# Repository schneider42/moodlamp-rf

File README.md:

# moodlamp
The moodlamp allows to change color in RGB colorspace.

Some art has been done with the help of moodlamps:
- ACAB (AllColourAreBeautiful) https://wiki.muc.ccc.de/acab:start
- Die Drei C https://wiki.muc.ccc.de/diedreic

# r3 version and earlier versions
Earlier versions are developed with ATmega324P, ATmega644P, ... For RS485 usage, change the MCU section in the file ubloader/Makefile.

# r4 version (2th quarter 2015)
Latest r4 version is designed with ATmega324A. If you get a warning from avrdude "device signature [..] expected signature [..] or use -F to override this check", put the following lines in your avrdude.conf:
```diff
 #------------------------------------------------------------
+# ATmega324A
+#------------------------------------------------------------
+
+# similar to ATmega324P
+
+part parent "m324p"
+    id               = "m324a";
+    desc             = "ATmega324A";
+    signature        = 0x1e 0x95 0x15;
+
+    ocdrev           = 3;
+  ;
+
+#------------------------------------------------------------
 # ATmega324PA
 #------------------------------------------------------------
```
For RS485 usage, also double check the MCU part in the file ubloader/Makefile.

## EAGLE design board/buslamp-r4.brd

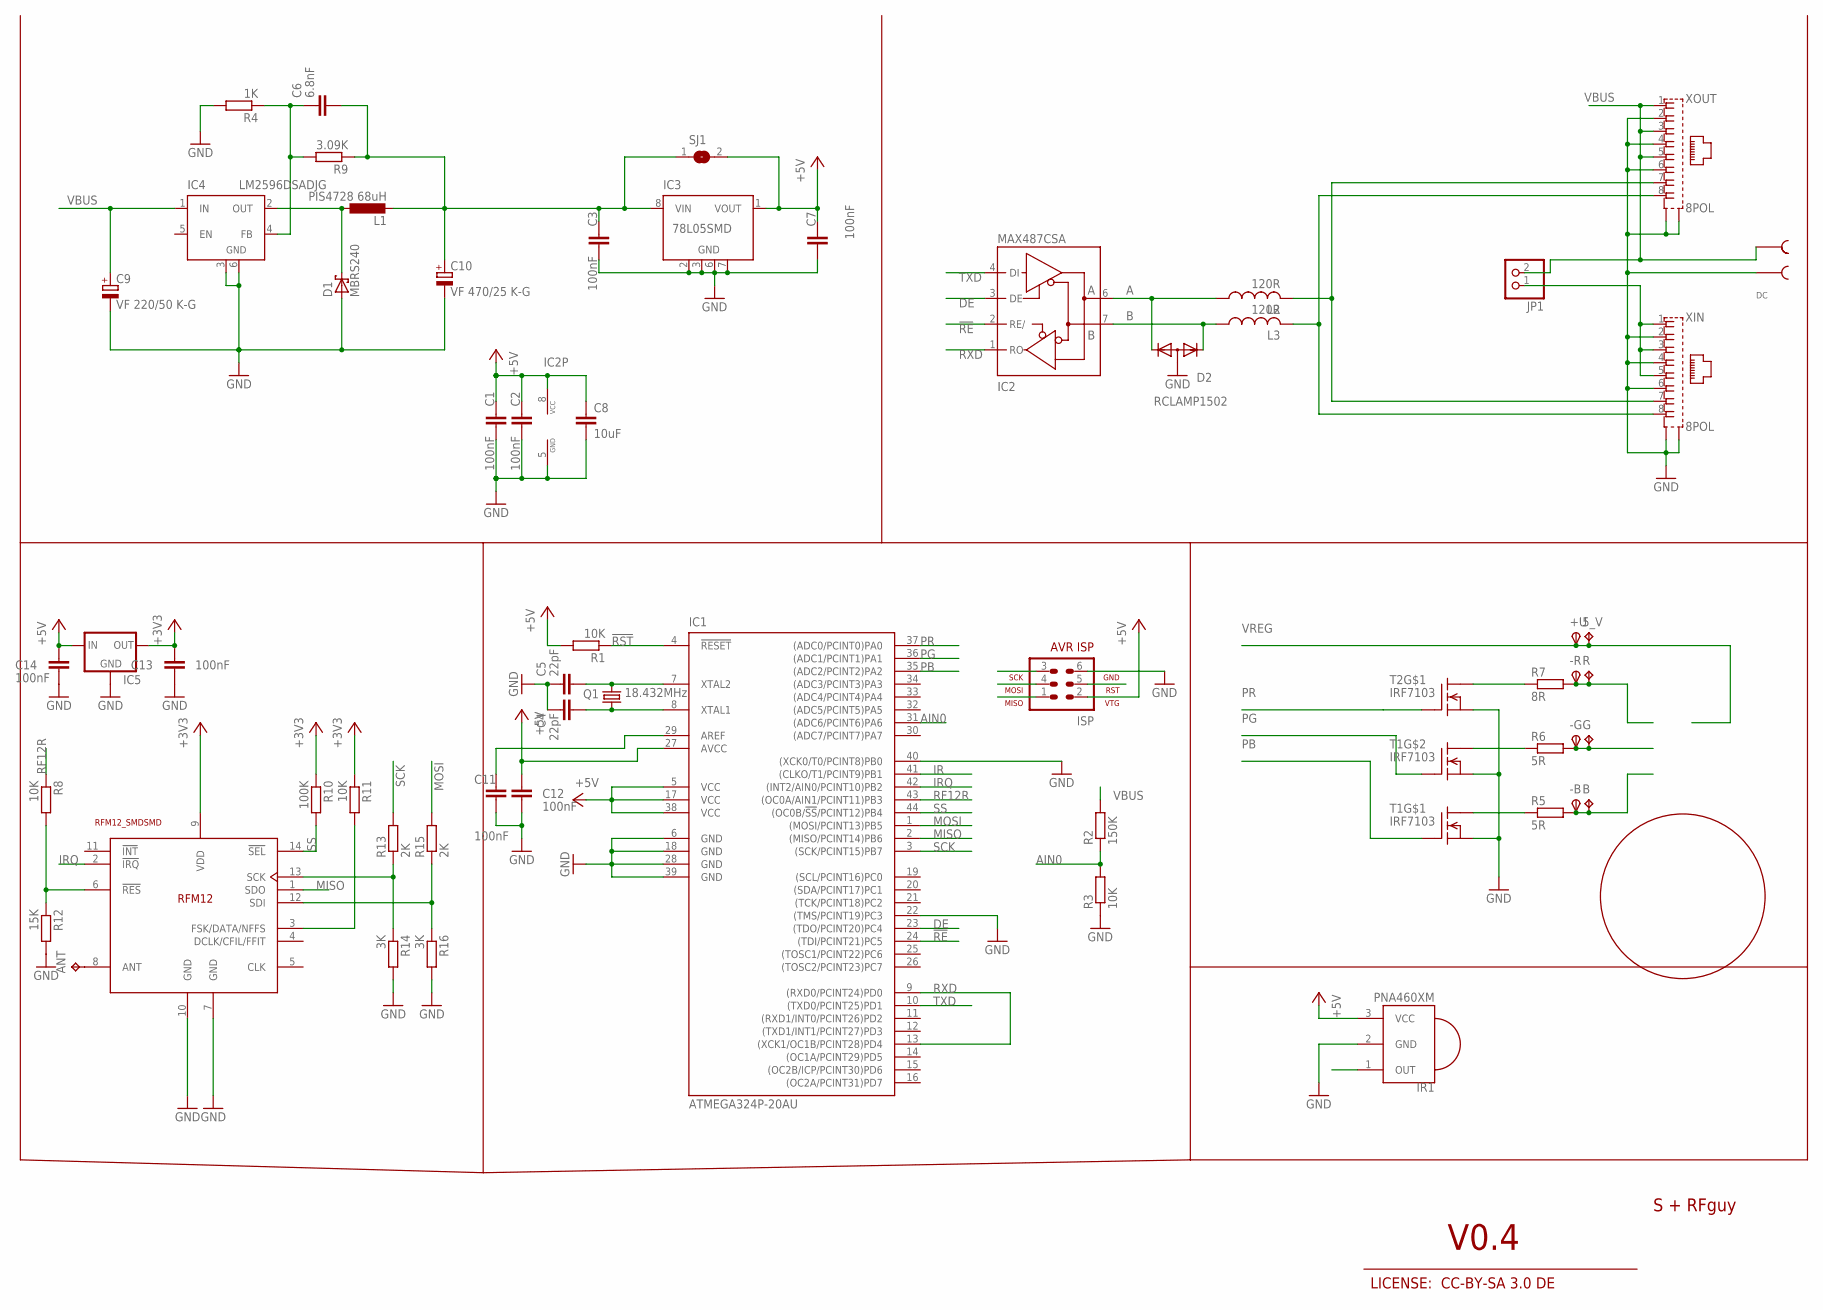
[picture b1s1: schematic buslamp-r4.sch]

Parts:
5_V: TPPAD1-13; P1-13
+U: TPSTP212R; TP212R
-B: TPSTP212R; TP212R
-G: TPSTP212R; TP212R
-R: TPSTP212R; TP212R
ANT: TPPAD1-13; P1-13
B: TPPAD1-13; P1-13
C1, C2, C3, C7: 100nF; C0805K
C4, C5: 22pF; C0805K
C6: 6.8nF; C0805K
C8: 10uF; C1210
C9: VF 220/50 K-G; UD-10X10_NICHICON
C10: VF 470/25 K-G; UD-10X10_NICHICON
C11, C12, C13, C14: 100nF; C0805
D1: MBRS240; SMB
D2: RCLAMP1502; SOT23
DC: STL-266-2
G: TPPAD1-13; P1-13
IC1: ATMEGA324P-20AU; TQFP44
IC2: MAX487CSA; SO08
IC3: 78L05SMD; SO08
IC4: LM2596DSADJG; TO263-5
IC5: MCP1700SOT23; SOT23
IR1: PNA460XM
ISP: AVR-ISP-6
JP1: PINHD-1X2; 1X02
L1: PIS4728 68uH; PIS4728
L2, L3: 120R; L0603
Q1: 18.432MHz; HC49/S
R: TPPAD1-13; P1-13
R1, R8, R11: 10K; M0805
R2: 150K; R0805
R3: 10K; R0805
R4: 1K; M0805
R5, R6: 5R; 0617/17
R7: 8R; 0617/17
R9: 3.09K; M0805
R10: 100K; M0805
R12: 15K; M0805
R13, R15: 2K; M0805
R14, R16: 3K; M0805
RF1: RFM12_SMDSMD; RFM12
SJ1: SJ
T1, T2: IRF7103; SO-8
U$2: KK-STERN; STERN
XIN: 8POL
XOUT: 8POL

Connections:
!RE: IC1.24 ((TDI/PCINT21)PC5), IC2.2 (RE/)
!RST: IC1.4 (!RESET), ISP.5, R1.1
+3V3: C13.2, IC5.2 (OUT), R10.1, R11.1, RF1.9 (VDD)
+5V: C1.1, C2.1, C7.1, C8.1, C12.2, C14.2, IC1.5 (VCC), IC1.17 (VCC), IC1.27 (AVCC), IC1.38 (VCC), IC2.8 (VCC), IC3.1 (VOUT), IC5.3 (IN), IR1.3 (VCC), ISP.2, R1.2, SJ1.2
A: L2.2, XIN.7, XOUT.7
AIN0: IC1.31 ((ADC6/PCINT6)PA6), R2.1, R3.2
B: L3.2, XIN.8, XOUT.8
DE: IC1.23 ((TDO/PCINT20)PC4), IC2.3 (DE)
G: -G.TP, G.TP, R6.2
GND: C1.2, C2.2, C3.2, C4.1, C5.1, C7.2, C8.2, C9.-, C10.-, C11.1, C12.1, C13.1, C14.1, D1.A, D2.3 (A), DC.P$3, IC1.6 (GND), IC1.18 (GND), IC1.22 ((TMS/PCINT19)PC3), IC1.28 (GND), IC1.39 (GND), IC1.40 ((XCK0/T0/PCINT8)PB0), IC2.5 (GND), IC3.2 (GND), IC3.3 (GND), IC3.6 (GND), IC3.7 (GND), IC4.3 (GND), IC4.6 (GND), IC5.1 (GND), IR1.2 (GND), ISP.6, R3.1, R4.2, R12.2, R14.2, R16.2, RF1.7 (GND), RF1.10 (GND), T1.1 (S), T1.3 (S), T2.1 (S), XIN.2, XIN.4, XIN.6, XIN.S1, XIN.S2, XOUT.2, XOUT.4, XOUT.6, XOUT.S1, XOUT.S2
IR: IC1.41 ((CLKO/T1/PCINT9)PB1), IR1.1 (OUT)
IRQ: IC1.42 ((INT2/AIN0/PCINT10)PB2), RF1.2 (!IRQ)
MISO: IC1.2 ((MISO/PCINT14)PB6), ISP.1, RF1.1 (SDO)
MOSI: IC1.1 ((MOSI/PCINT13)PB5), ISP.4, R15.2
unnamed: R7.1, T2.8 (D1)
unnamed: R8.2, R12.1, RF1.6 (!RES)
unnamed: C6.1, IC4.4 (FB), R4.1, R9.2
unnamed: R6.1, T1.5 (D1)
unnamed: R5.1, T1.8 (D1)
unnamed: -B.TP, B.TP, R5.2
unnamed: R13.1, R14.1, RF1.13 (SCK)
unnamed: R15.1, R16.1, RF1.12 (SDI)
unnamed: ANT.TP, RF1.8 (ANT)
unnamed: D1.C, IC4.2 (OUT), L1.1
unnamed: D2.2 (K2), IC2.6 (A), L2.1
unnamed: D2.1 (K1), IC2.7 (B), L3.1
unnamed: R11.2, RF1.3 (FSK/DATA/NFFS)
unnamed: C11.2, IC1.29 (AREF)
PB: IC1.35 ((ADC2/PCINT2)PA2), T1.2 (G)
PG: IC1.36 ((ADC1/PCINT1)PA1), T1.4 (G)
PR: IC1.37 ((ADC0/PCINT0)PA0), T2.2 (G)
R: -R.TP, R.TP, R7.2
RF12R: IC1.43 ((OC0A/AIN1/PCINT11)PB3), R8.1
RXD: IC1.9 ((RXD0/PCINT24)PD0), IC1.13 ((XCK1/OC1B/PCINT28)PD4), IC2.1 (RO)
SCK: IC1.3 ((SCK/PCINT15)PB7), ISP.3, R13.2
SS: IC1.44 ((OC0B/!SS!/PCINT12)PB4), R10.2, RF1.14 (!SEL)
TXD: IC1.10 ((TXD0/PCINT25)PD1), IC2.4 (DI)
VBUS: C9.+, DC.P$4, IC4.1 (IN), JP1.2, R2.2, XOUT.1, XOUT.3, XOUT.5
VBUSOUT: JP1.1, XIN.1, XIN.3, XIN.5
VREG: 5_V.TP, +U.TP, C3.1, C6.2, C10.+, IC3.8 (VIN), L1.2, R9.1, SJ1.1
XTAL1: C5.2, IC1.7 (XTAL2), Q1.2
XTAL2: C4.2, IC1.8 (XTAL1), Q1.1

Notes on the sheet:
S + RFguy
V0.4
LICENSE: CC-BY-SA 3.0 DE
RF12R
IRQ
MOSI
MISO
SCK

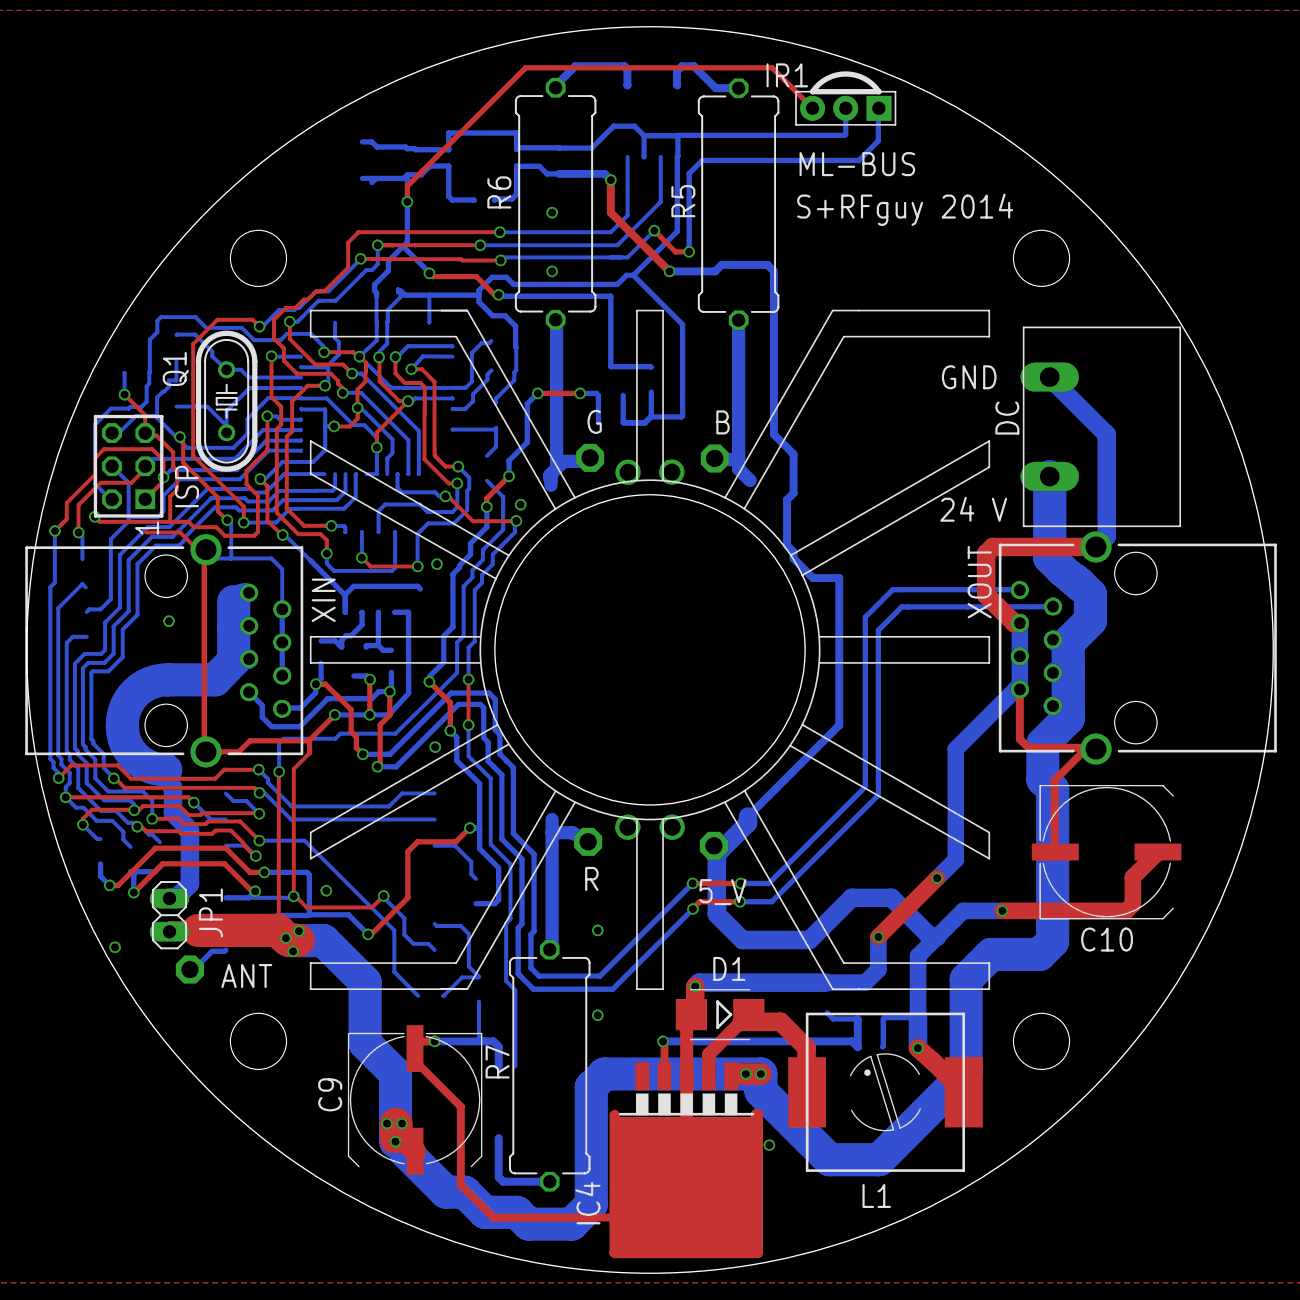
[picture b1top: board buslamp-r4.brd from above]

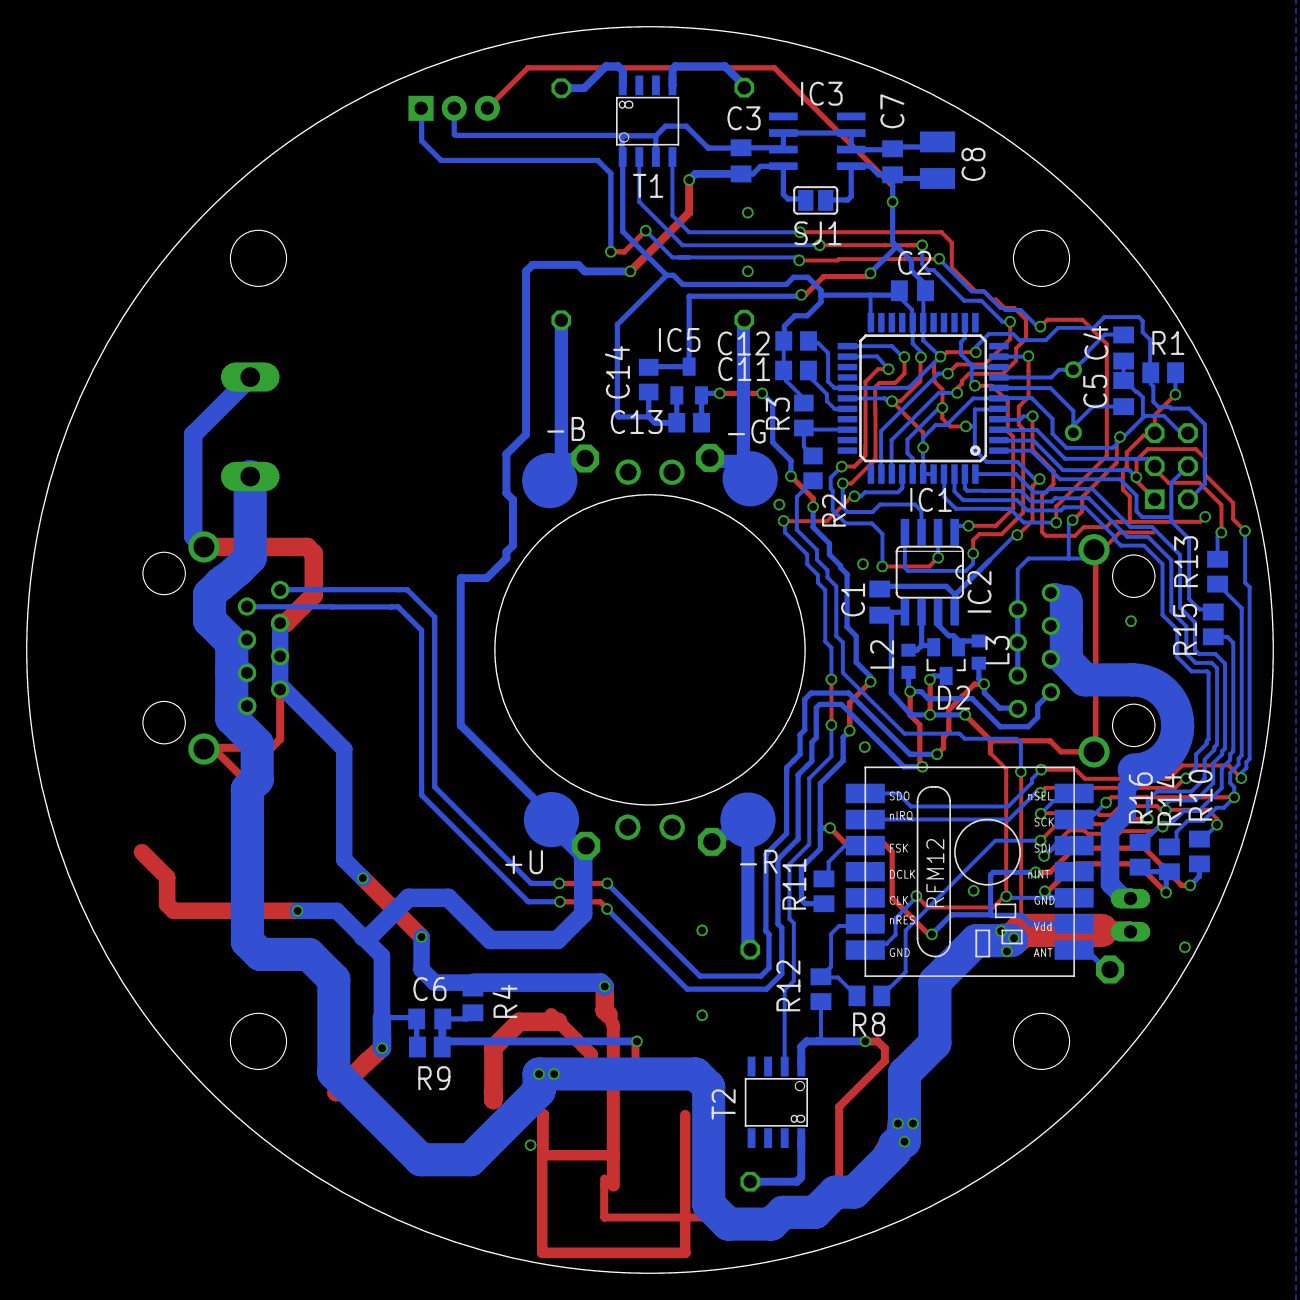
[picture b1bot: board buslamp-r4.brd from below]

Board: 2 copper layers, 95.5 x 95.5 mm, 61 parts (40 on the bottom side), 42 nets.

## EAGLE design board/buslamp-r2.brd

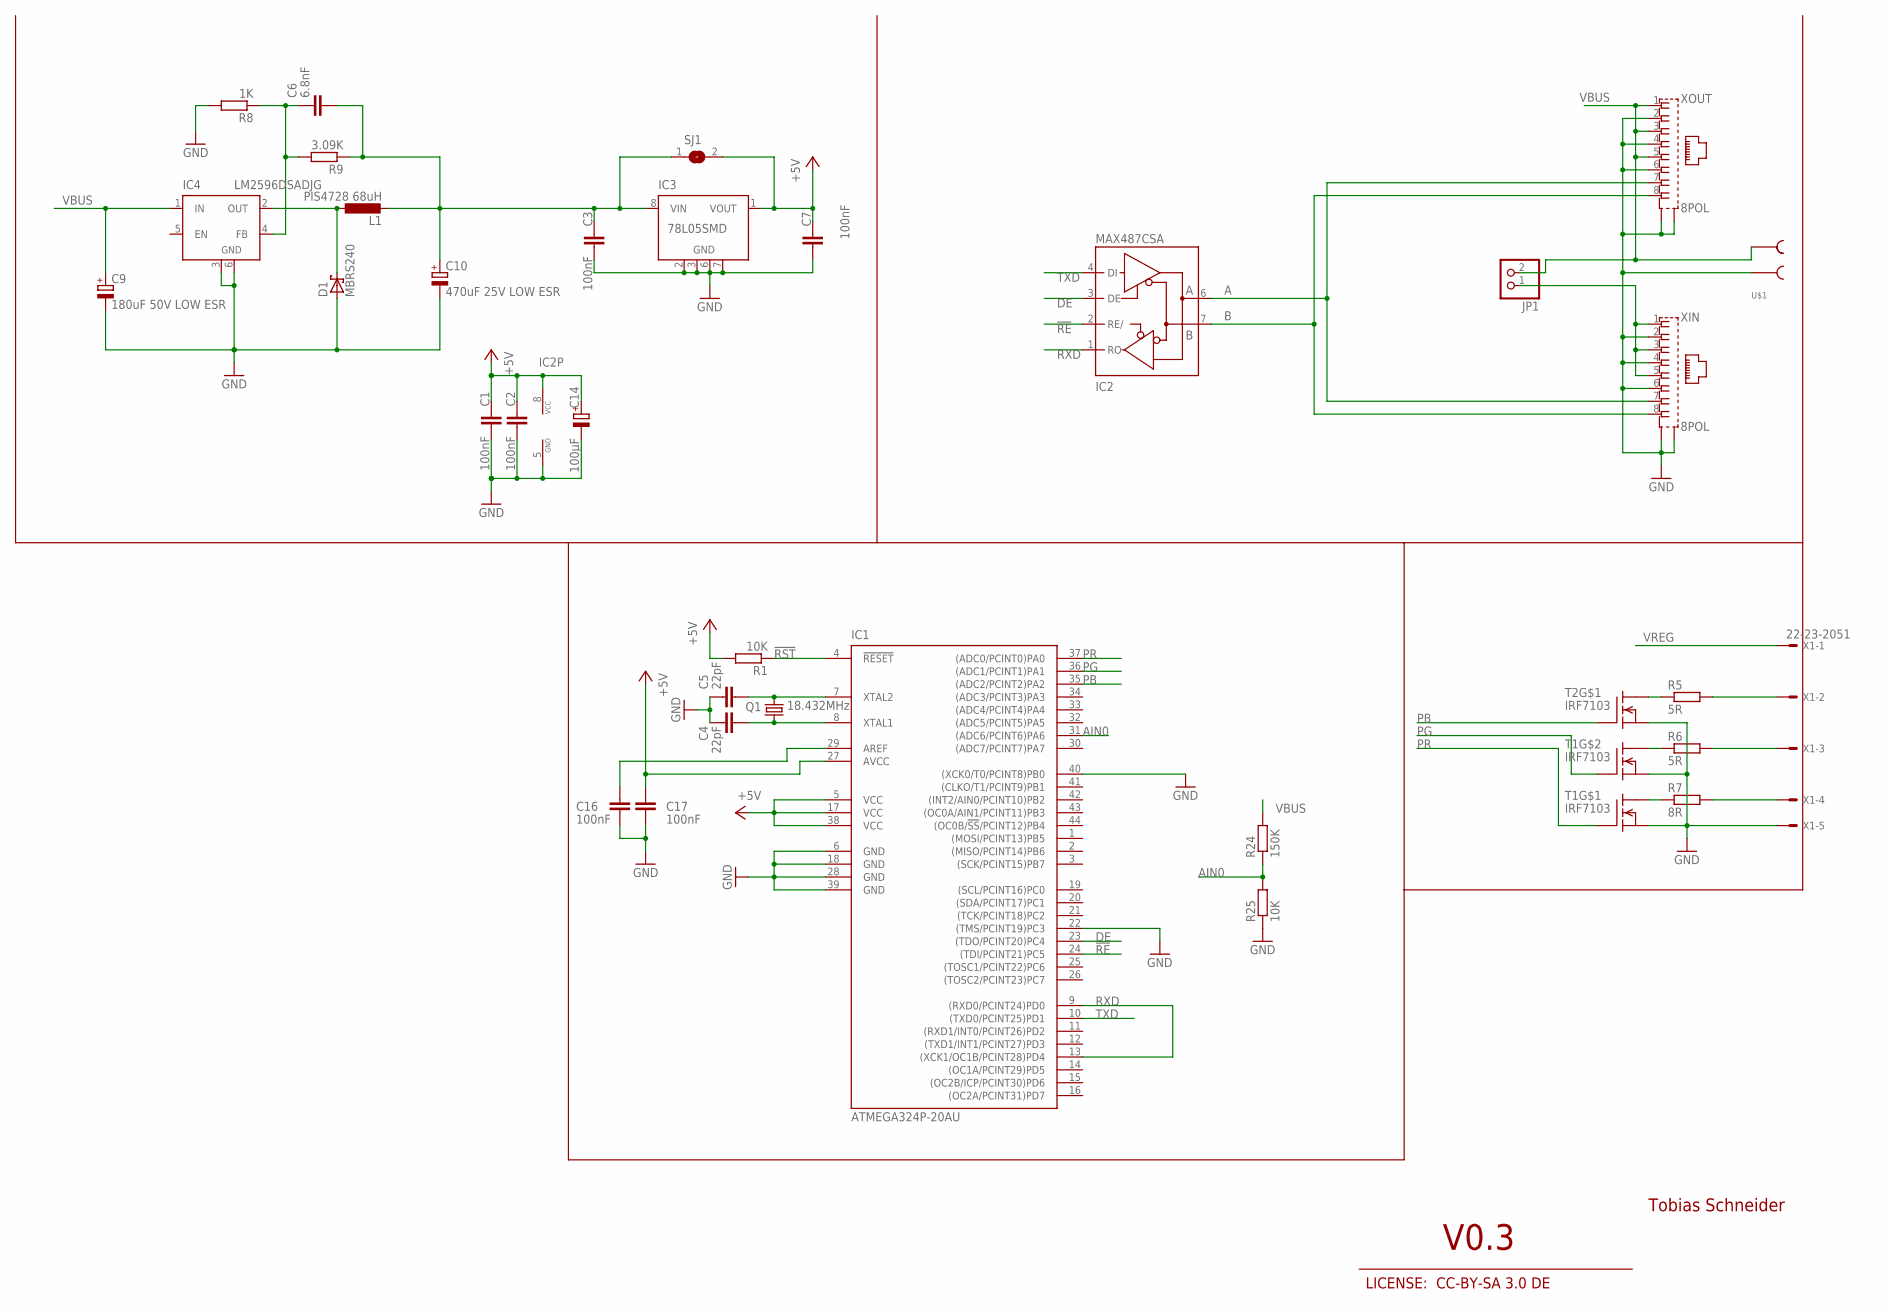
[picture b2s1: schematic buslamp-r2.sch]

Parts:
C1, C2, C3, C7: 100nF; C0805K
C4, C5: 22pF; C0805K
C6: 6.8nF; C0805K
C9: 180uF 50V LOW ESR; E3,5-8
C10: 470uF 25V LOW ESR; E2,5-7
C14: 100µF; E2,5-6
C16, C17: 100nF; C0805
D1: MBRS240; SMB
IC1: ATMEGA324P-20AU; TQFP44
IC2: MAX487CSA; SO08
IC3: 78L05SMD; SO08
IC4: LM2596DSADJG; TO263-5
JP1: PINHD-1X2; 1X02
L1: PIS4728 68uH; PIS4728
Q1: 18.432MHz; HC49/S
R1: 10K; M0805
R5, R6: 5R; 0617/17
R7: 8R; 0617/17
R8: 1K; M0805
R9: 3.09K; M0805
R24: 150K; R0805
R25: 10K; R0805
SJ1: SJ
T1, T2: IRF7103; SO-8
U$1: STL-266-2
X1: 22-23-2051
XIN: 8POL
XOUT: 8POL

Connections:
!RE: IC1.24 ((TDI/PCINT21)PC5), IC2.2 (RE/)
!RST: IC1.4 (!RESET), R1.1
+5V: C1.1, C2.1, C7.1, C14.+, C17.2, IC1.5 (VCC), IC1.17 (VCC), IC1.27 (AVCC), IC1.38 (VCC), IC2.8 (VCC), IC3.1 (VOUT), R1.2, SJ1.2
A: IC2.6 (A), XIN.7, XOUT.7
AIN0: IC1.31 ((ADC6/PCINT6)PA6), R24.1, R25.2
B: IC2.7 (B), XIN.8, XOUT.8
DE: IC1.23 ((TDO/PCINT20)PC4), IC2.3 (DE)
GND: C1.2, C2.2, C3.2, C4.1, C5.1, C7.2, C9.-, C10.-, C14.-, C16.1, C17.1, D1.A, IC1.6 (GND), IC1.18 (GND), IC1.22 ((TMS/PCINT19)PC3), IC1.28 (GND), IC1.39 (GND), IC1.40 ((XCK0/T0/PCINT8)PB0), IC2.5 (GND), IC3.2 (GND), IC3.3 (GND), IC3.6 (GND), IC3.7 (GND), IC4.3 (GND), IC4.6 (GND), R8.2, R25.1, T1.1 (S), T1.3 (S), T2.1 (S), U$1.P$3, X1.5, XIN.2, XIN.4, XIN.6, XIN.S1, XIN.S2, XOUT.2, XOUT.4, XOUT.6, XOUT.S1, XOUT.S2
unnamed: R7.1, T1.8 (D1)
unnamed: C6.1, IC4.4 (FB), R8.1, R9.2
unnamed: R6.1, T1.5 (D1)
unnamed: R5.1, T2.8 (D1)
unnamed: R7.2, X1.4
unnamed: R6.2, X1.3
unnamed: R5.2, X1.2
unnamed: D1.C, IC4.2 (OUT), L1.1
unnamed: C16.2, IC1.29 (AREF)
PB: IC1.35 ((ADC2/PCINT2)PA2), T2.2 (G)
PG: IC1.36 ((ADC1/PCINT1)PA1), T1.4 (G)
PR: IC1.37 ((ADC0/PCINT0)PA0), T1.2 (G)
RXD: IC1.9 ((RXD0/PCINT24)PD0), IC1.13 ((XCK1/OC1B/PCINT28)PD4), IC2.1 (RO)
TXD: IC1.10 ((TXD0/PCINT25)PD1), IC2.4 (DI)
VBUS: C9.+, IC4.1 (IN), JP1.2, R24.2, U$1.P$4, XOUT.1, XOUT.3, XOUT.5
VBUSOUT: JP1.1, XIN.1, XIN.3, XIN.5
VREG: C3.1, C6.2, C10.+, IC3.8 (VIN), L1.2, R9.1, SJ1.1, X1.1
XTAL1: C5.2, IC1.7 (XTAL2), Q1.2
XTAL2: C4.2, IC1.8 (XTAL1), Q1.1

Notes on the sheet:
Tobias Schneider
V0.3
LICENSE: CC-BY-SA 3.0 DE

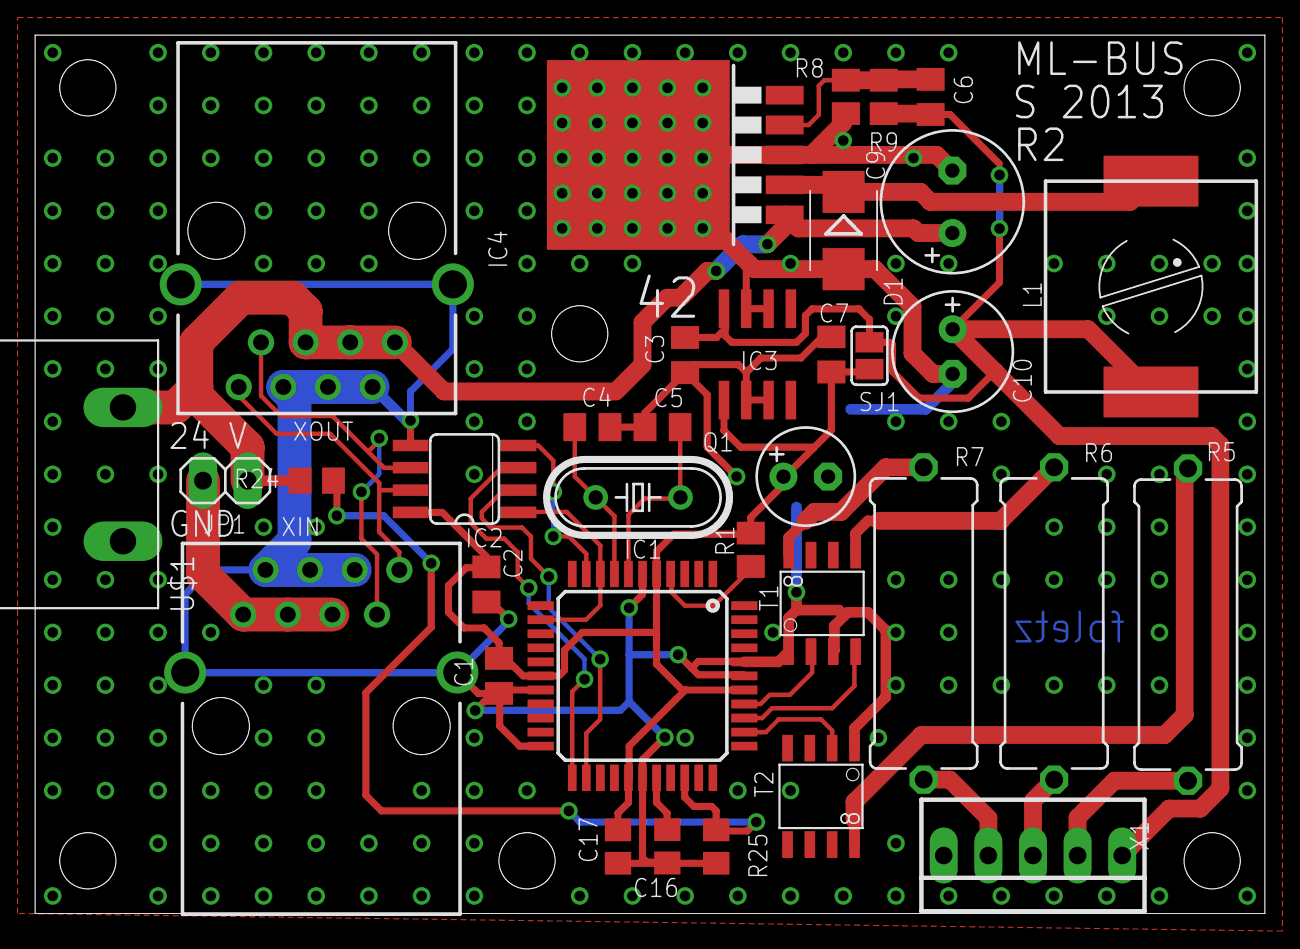
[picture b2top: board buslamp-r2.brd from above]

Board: 2 copper layers, 70.0 x 50.0 mm, 35 parts (0 on the bottom side), 27 nets.

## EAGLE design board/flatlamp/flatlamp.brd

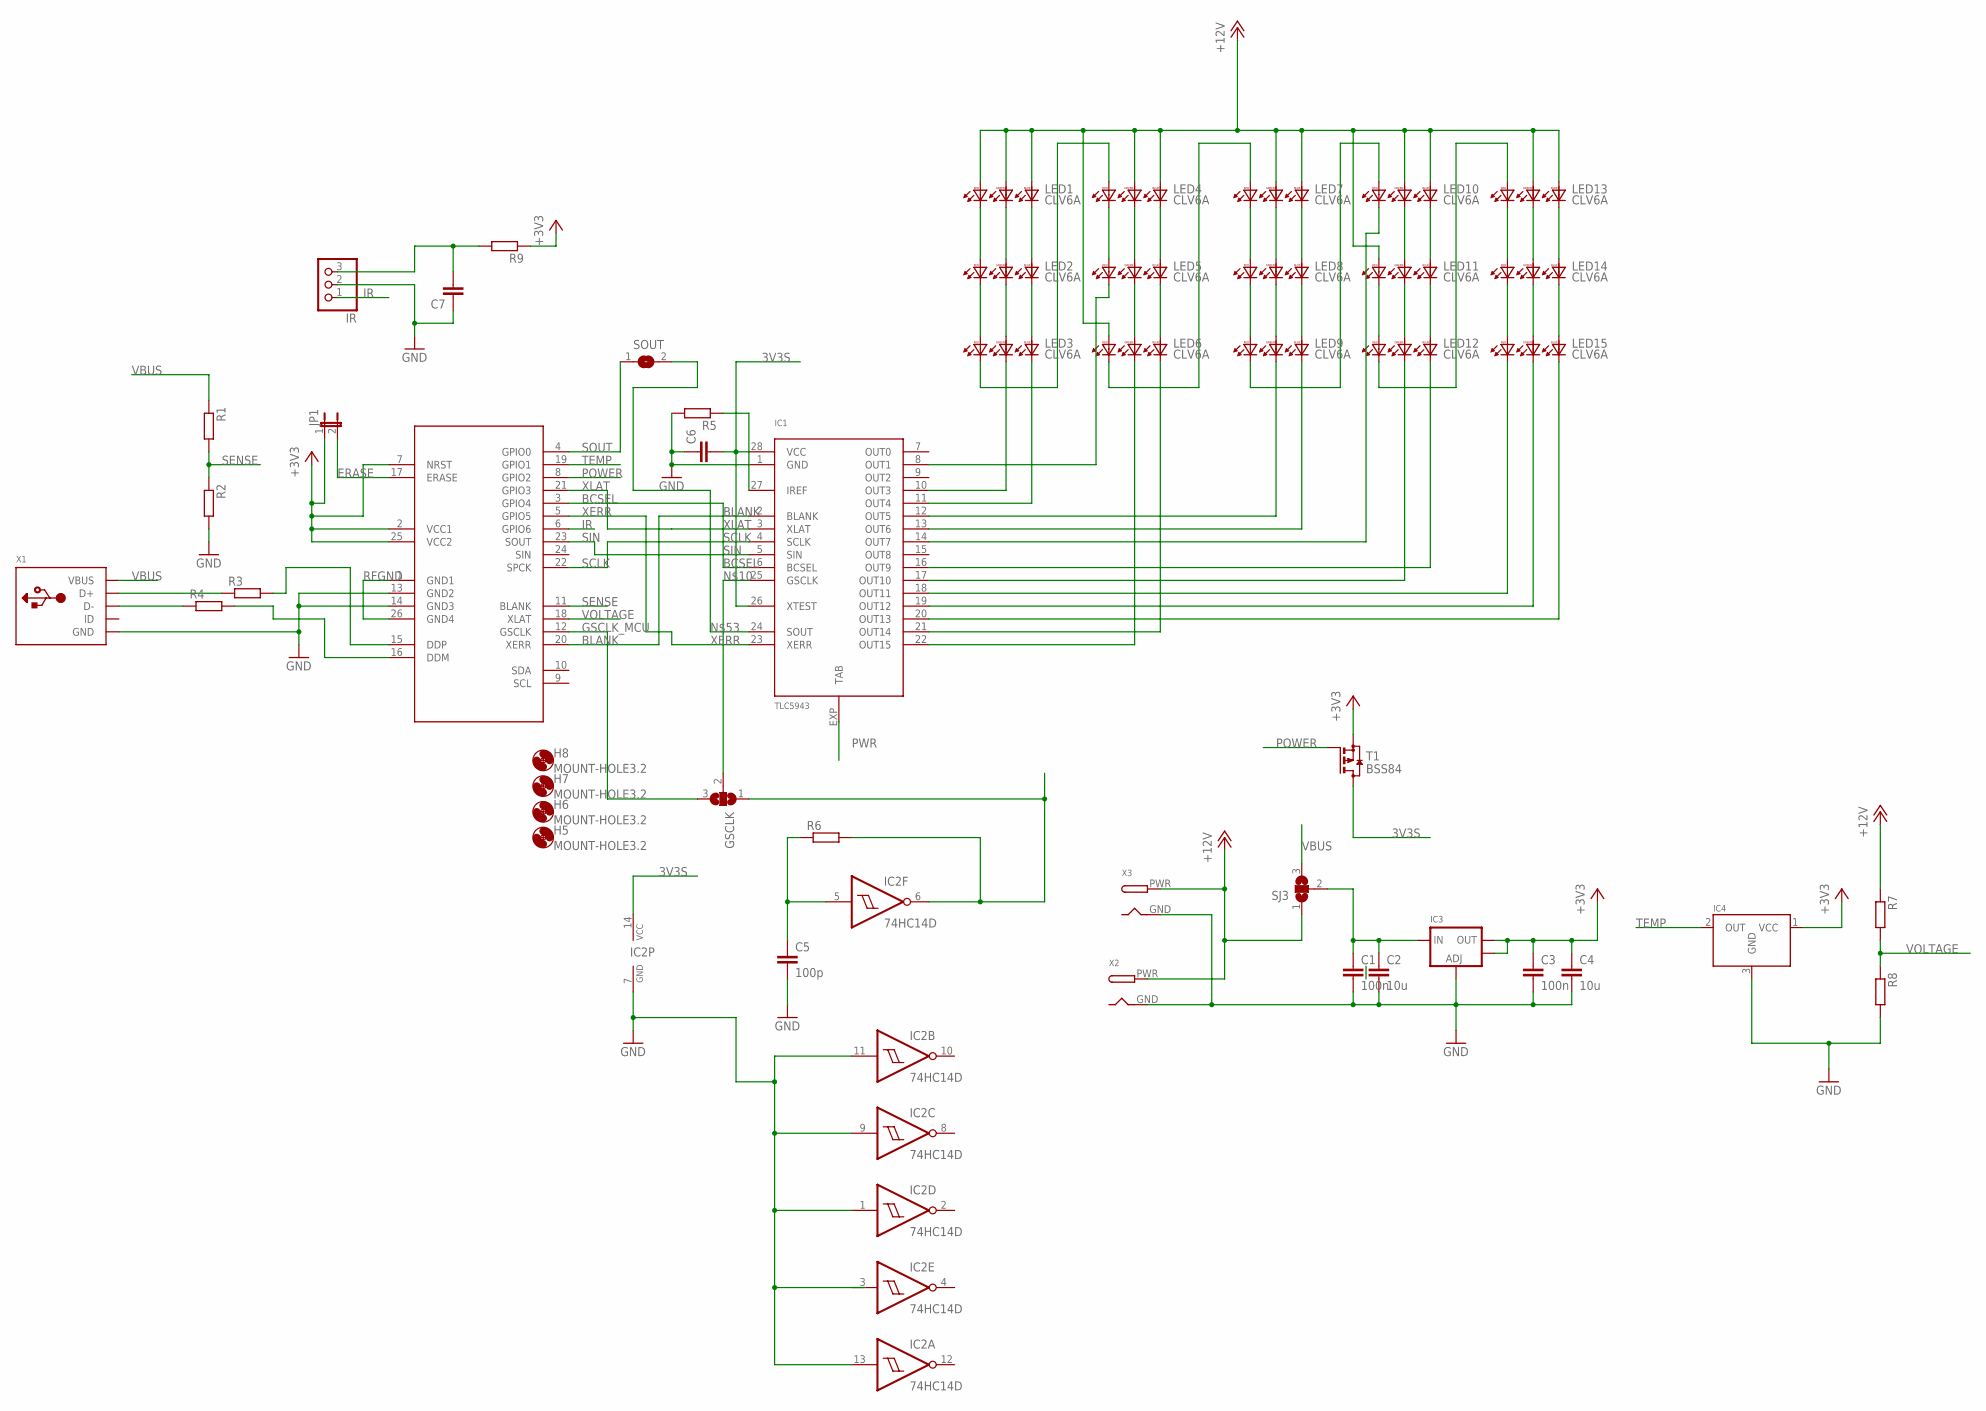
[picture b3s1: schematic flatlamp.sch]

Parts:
C1, C3: 100n; C0805
C2, C4: 10u; C0805
C5: 100p; C0805
C6, C7: C-EUC0805; C0805
GSCLK: SJ2W; SJ_2
H5, H6, H7, H8: MOUNT-HOLE3.2; 3,2
IC1: TLC5943; HTSSOP28PWP
IC2: 74HC14D; SO14
IC3: LM1117SOT223-REFLOW; SOT223-R
IC4: MCP9701T-E/TTCTREFLOW; SOT23-R
IR: PINHD-1X3; 1X03
JP1: JP1E; JP1
LED1, LED2, LED3, LED4, LED5, LED6, LED7, LED8, LED9, LED10, LED11, LED12, LED13, LED14, LED15: CLV6A; PLCC6
R1, R2, R3, R4, R5, R6, R7, R8, R9: R-EU_R0805; R0805
SJ3: SJ2W; SJ_2
SOUT: SJ
T1: BSS84; SOT23
U$1: RFBOARD
X1: USBMINIB; USB-MINIB
X2, X3: DCBARRELPTH; DCJACK_2MM_PTH

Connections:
3V3S: C6.2, IC1.26 (XTEST), IC1.28 (VCC), IC2.14 (VCC), T1.3 (D)
+3V3: C3.1, C4.1, IC3.2 (OUT), IC3.4 (OUT1), IC4.1 (VCC), JP1.1, R9.1, T1.2 (S), U$1.2 (VCC1), U$1.7 (NRST), U$1.25 (VCC2)
+12V: LED1.4 (RA), LED1.5 (GA), LED1.6 (BA), LED4.5 (GA), LED4.6 (BA), LED6.4 (RA), LED7.5 (GA), LED7.6 (BA), LED10.5 (GA), LED10.6 (BA), LED11.4 (RA), LED13.5 (GA), LED13.6 (BA), R7.1, SJ3.1, X2.PWR, X3.PWR
BCSEL: IC1.6 (BCSEL), U$1.3 (GPIO4)
BLANK: IC1.2 (BLANK), U$1.20 (XERR)
ERASE: JP1.2, U$1.17 (ERASE)
GND: C1.2, C2.2, C3.2, C4.2, C5.2, C6.1, C7.1, IC1.1 (GND), IC2.1 (I), IC2.7 (GND), IC2.9 (I), IC2.11 (I), IC2.13 (I), IC3.1 (ADJ), IC4.3 (GND), IR.2, R2.2, R5.2, R8.2, U$1.13 (GND2), U$1.14 (GND3), X1.GND, X2.GND, X3.GND
GSCLK_MCU: GSCLK.3, U$1.12 (GSCLK)
IR: IR.1, U$1.6 (GPIO6)
unnamed: LED1.3 (RC), LED2.4 (RA)
unnamed: LED1.2 (GC), LED2.5 (GA)
unnamed: LED1.1 (BC), LED2.6 (BA)
unnamed: LED2.3 (RC), LED3.4 (RA)
unnamed: LED2.2 (GC), LED3.5 (GA)
unnamed: LED2.1 (BC), LED3.6 (BA)
unnamed: LED4.3 (RC), LED5.4 (RA)
unnamed: LED4.2 (GC), LED5.5 (GA)
unnamed: LED4.1 (BC), LED5.6 (BA)
unnamed: GSCLK.2, IC1.25 (GSCLK)
unnamed: LED5.2 (GC), LED6.5 (GA)
unnamed: LED5.1 (BC), LED6.6 (BA)
unnamed: LED7.3 (RC), LED8.4 (RA)
unnamed: LED7.2 (GC), LED8.5 (GA)
unnamed: LED7.1 (BC), LED8.6 (BA)
unnamed: LED8.3 (RC), LED9.4 (RA)
unnamed: LED8.2 (GC), LED9.5 (GA)
unnamed: LED8.1 (BC), LED9.6 (BA)
unnamed: IC1.10 (OUT3), LED3.2 (GC)
unnamed: LED10.2 (GC), LED11.5 (GA)
unnamed: LED10.1 (BC), LED11.6 (BA)
unnamed: LED11.3 (RC), LED12.4 (RA)
unnamed: LED11.2 (GC), LED12.5 (GA)
unnamed: LED11.1 (BC), LED12.6 (BA)
unnamed: LED13.3 (RC), LED14.4 (RA)
unnamed: LED13.2 (GC), LED14.5 (GA)
unnamed: LED13.1 (BC), LED14.6 (BA)
unnamed: LED14.3 (RC), LED15.4 (RA)
unnamed: LED14.2 (GC), LED15.5 (GA)
unnamed: LED14.1 (BC), LED15.6 (BA)
unnamed: LED3.3 (RC), LED4.4 (RA)
unnamed: LED6.3 (RC), LED7.4 (RA)
unnamed: LED9.3 (RC), LED10.4 (RA)
unnamed: LED12.3 (RC), LED13.4 (RA)
unnamed: IC1.11 (OUT4), LED3.1 (BC)
unnamed: IC1.8 (OUT1), LED5.3 (RC)
unnamed: IC1.22 (OUT15), LED6.2 (GC)
unnamed: IC1.21 (OUT14), LED6.1 (BC)
unnamed: IC1.12 (OUT5), LED9.2 (GC)
unnamed: IC1.13 (OUT6), LED9.1 (BC)
unnamed: IC1.14 (OUT7), LED10.3 (RC)
unnamed: IC1.17 (OUT10), LED12.2 (GC)
unnamed: IC1.16 (OUT9), LED12.1 (BC)
unnamed: IC1.18 (OUT11), LED15.3 (RC)
unnamed: IC1.19 (OUT12), LED15.2 (GC)
unnamed: IC1.20 (OUT13), LED15.1 (BC)
unnamed: R4.2, U$1.16 (DDM)
unnamed: GSCLK.1, IC2.6 (O), R6.2
unnamed: IC1.24 (SOUT), SOUT.2
unnamed: R3.2, U$1.15 (DDP)
unnamed: IC1.27 (IREF), R5.1
unnamed: C5.1, IC2.5 (I), R6.1
unnamed: R3.1, X1.D+
unnamed: C1.1, C2.1, IC3.3 (IN), SJ3.2
unnamed: R4.1, X1.D-
unnamed: C7.2, IR.3, R9.2
POWER: T1.1 (G), U$1.8 (GPIO2)
PWR: IC1.EXP (TAB)
RFGND: U$1.1 (GND1), U$1.26 (GND4)
SCLK: IC1.4 (SCLK), U$1.22 (SPCK)
SENSE: R1.2, R2.1, U$1.11 (BLANK)
SIN: IC1.5 (SIN), U$1.23 (SOUT)
SOUT: SOUT.1, U$1.4 (GPIO0)
TEMP: IC4.2 (OUT), U$1.19 (GPIO1)
VBUS: R1.1, SJ3.3, X1.VBUS
VOLTAGE: R7.2, R8.1, U$1.18 (XLAT)
XERR: IC1.23 (XERR), U$1.5 (GPIO5)
XLAT: IC1.3 (XLAT), U$1.21 (GPIO3)

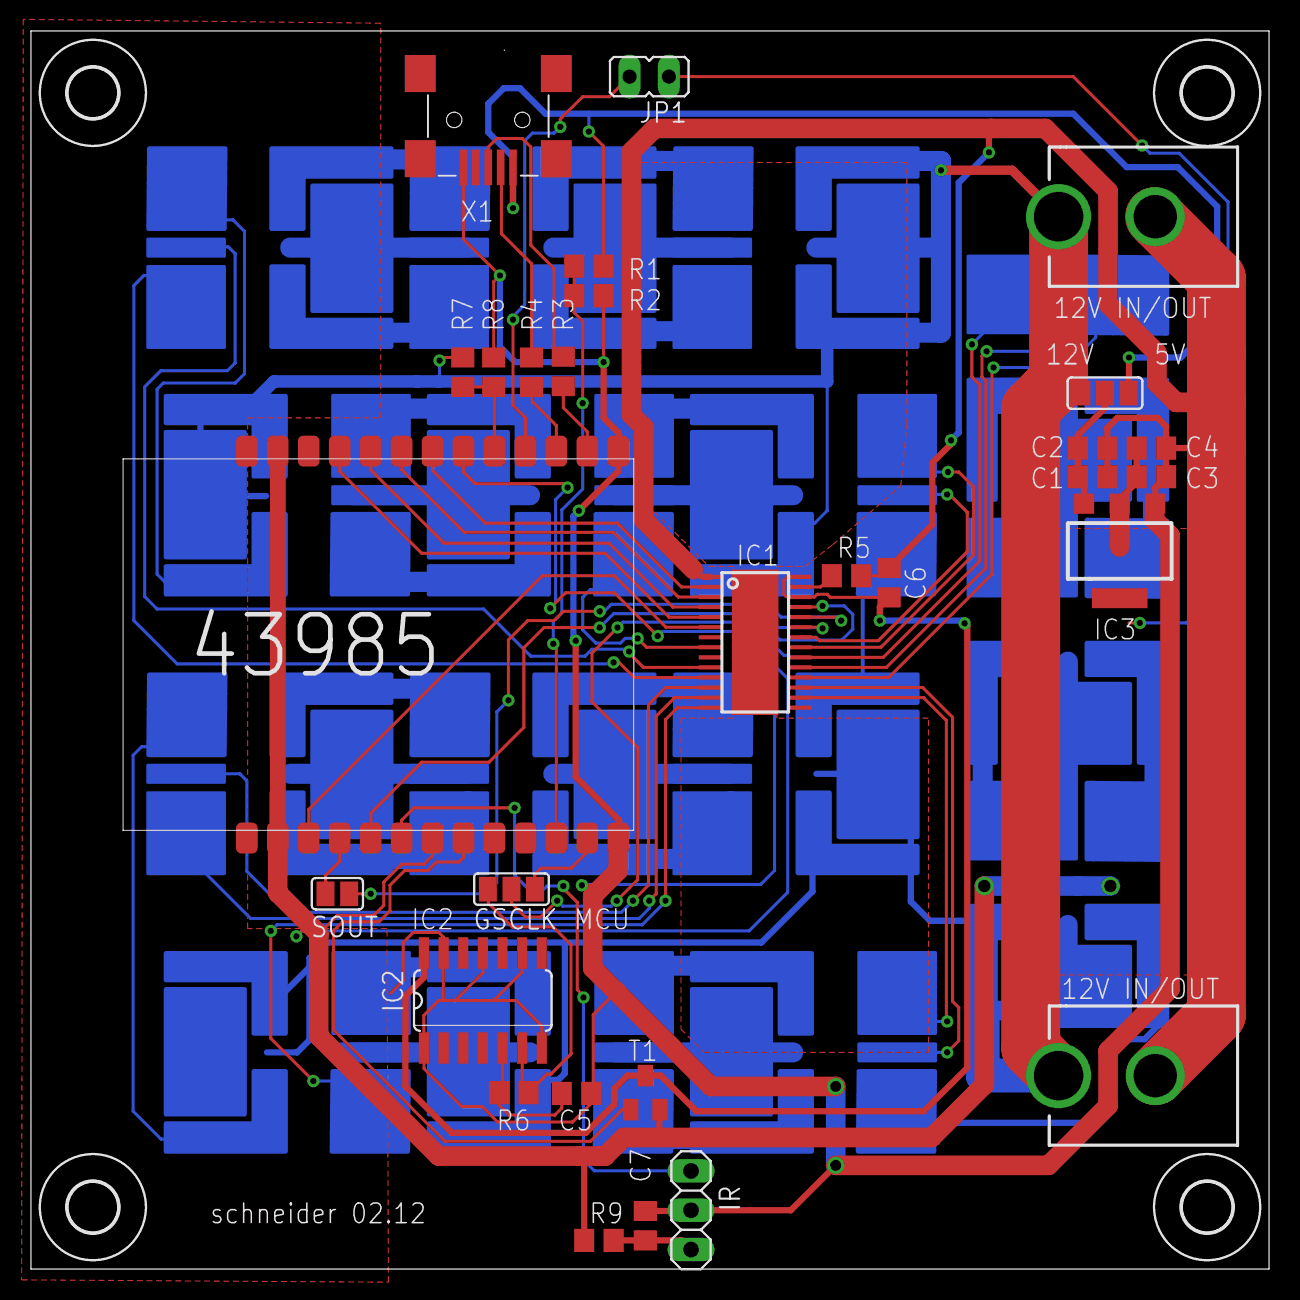
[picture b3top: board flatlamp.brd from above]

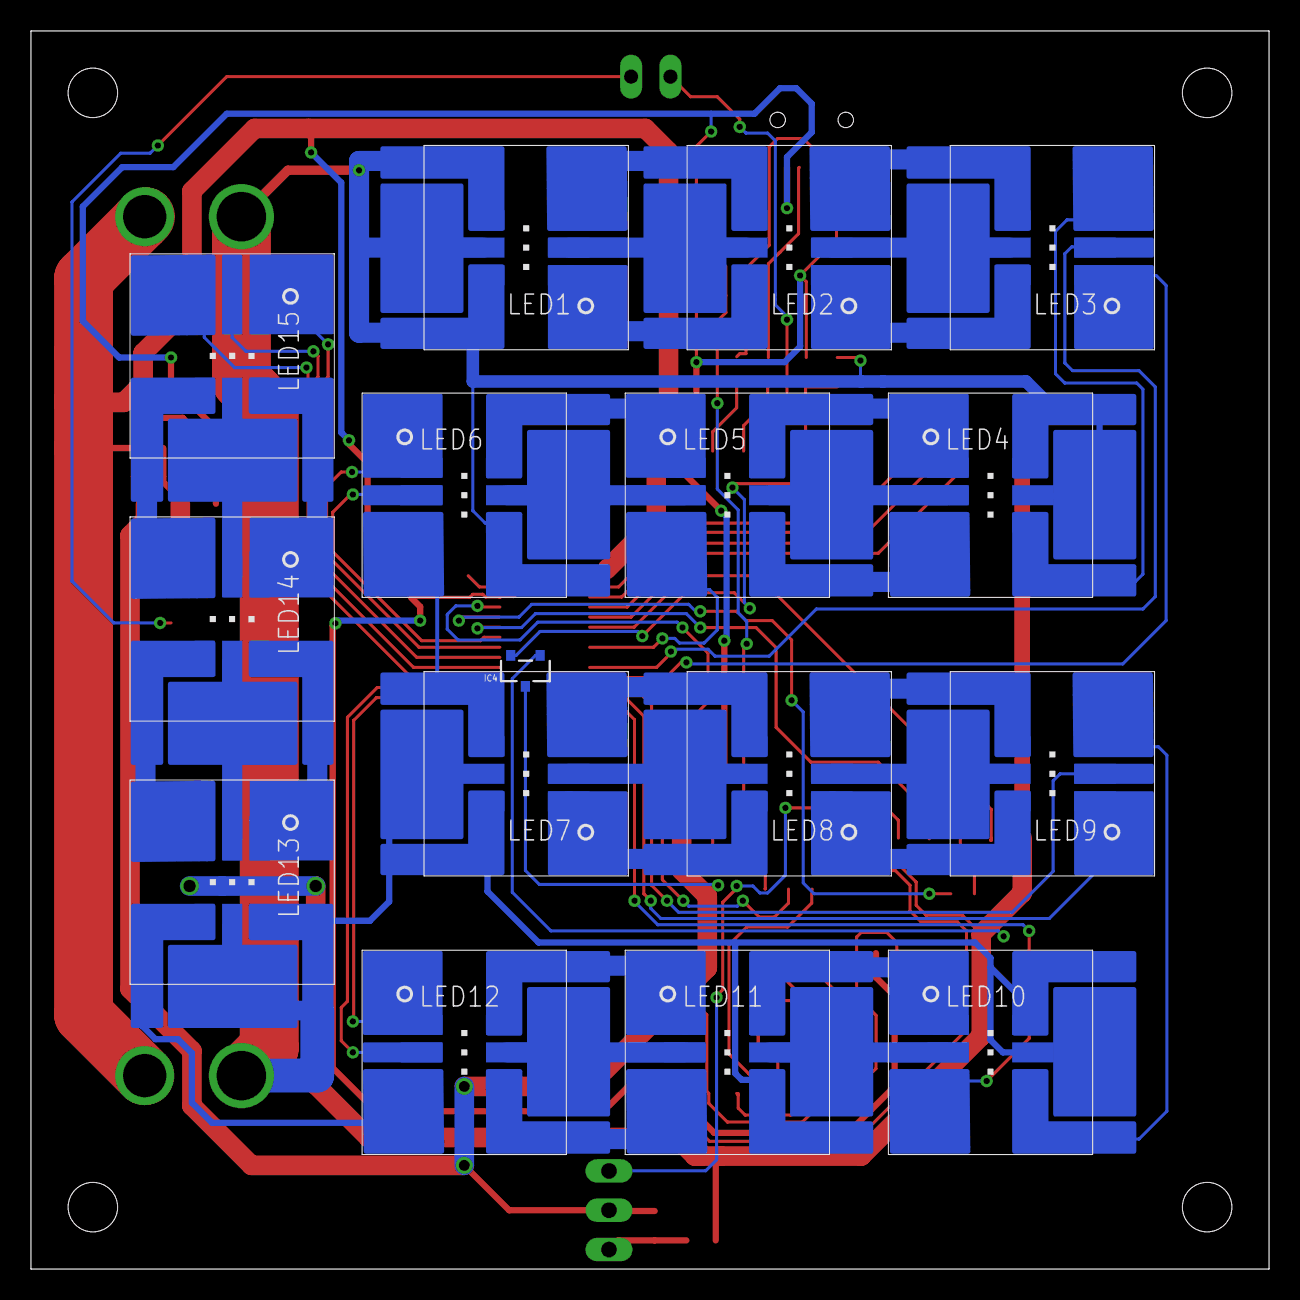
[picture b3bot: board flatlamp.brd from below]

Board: 2 copper layers, 80.0 x 80.0 mm, 49 parts (16 on the bottom side), 76 nets.
